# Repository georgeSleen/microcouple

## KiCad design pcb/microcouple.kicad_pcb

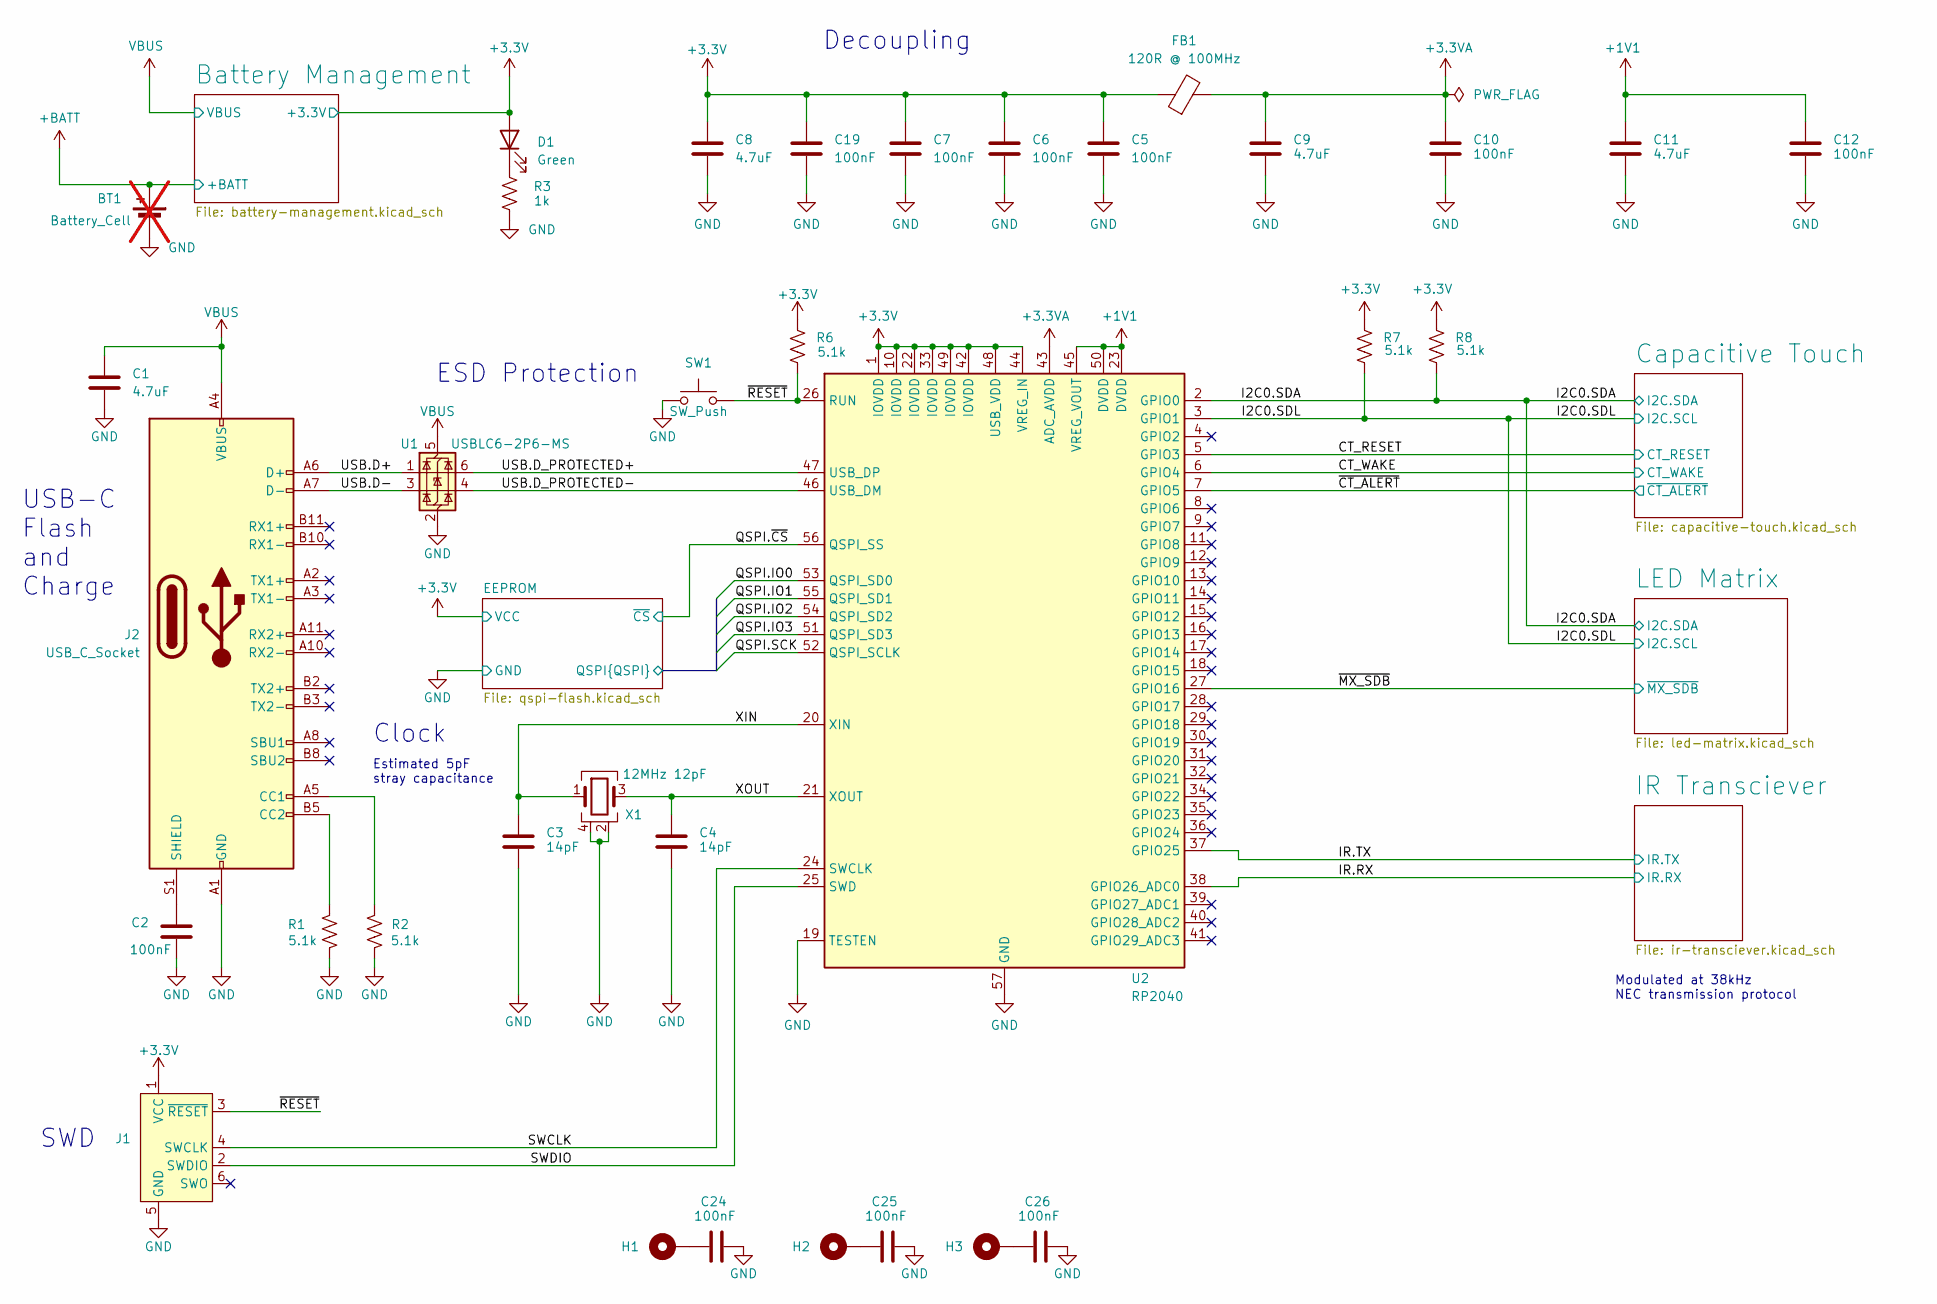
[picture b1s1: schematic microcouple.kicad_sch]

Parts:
BT1: Battery_Cell; PinSocket_2x01_P1.27mm_Vertical; not fitted
C1, C8, C9, C11: 4.7uF; C_0402_1005Metric; Mfr. Part # GRM155R60J475ME87D; LCSC ID C76996
C2, C5, C6, C7, C10, C12, C19, C24, C25, C26: 100nF; C_0402_1005Metric; Mfr. Part # TCC0402X5R104K160AT; LCSC ID C344189
C3, C4: 14pF; C_0402_1005Metric; Mfr. Part # 0402CG140J500NT; LCSC ID C3037644
D1: Green; LED_0402_1005Metric; Mfr. Part # XL-1005UGC; LCSC ID C965793
FB1: 120R @ 100MHz; L_0805_2012Metric; Mfr. Part # HCB2012KF-121T30; LCSC ID C356987
H1, H2, H3: MountingHole_Pad; MountingHole_2.2mm_M2_DIN965_Pad
J1: Conn_ARM_SWD_TagConnect_TC2030-NL; Tag-Connect_TC2030-IDC-NL_2x03_P1.27mm_Vertical
J2: USB_C_Socket; USB-C-SMD; Mfr. Part # TYPE-C 24P QT; LCSC ID C2681555
R1, R2, R6, R7, R8: 5.1k; R_0402_1005Metric; Mfr. Part # RC-02K512JT; LCSC ID C453708
R3: 1k; R_0402_1005Metric; Mfr. Part # FRC0402J102 TS; LCSC ID C2906899
SW1: SW_Push; SW_SPST_B3U-1000P; Mfr. Part # B3U-1000P; LCSC ID C231329
U1: USBLC6-2P6-MS; SOT-666; Mfr. Part # USBLC6-2P6; LCSC ID C2827693
U2: RP2040; QFN-56-1EP_7x7mm_P0.4mm_EP3.2x3.2mm; Mfr. Part # RP2040; LCSC ID C2040
X1: 12MHz 12pF; Crystal_SMD_3225-4Pin_3.2x2.5mm; Mfr. Part # TAXM12M4RFBCCT2T; LCSC ID C133337

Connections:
+1V1: C11.1, C12.1, U2.23 (DVDD), U2.45 (VREG_VOUT), U2.50 (DVDD)
+3.3V: C5.1, C6.1, C7.1, C8.1, C19.1, D1.2 (A), FB1.1, J1.1 (VCC), R6.1, R7.1, R8.1, U2.1 (IOVDD), U2.10 (IOVDD), U2.22 (IOVDD), U2.33 (IOVDD), U2.42 (IOVDD), U2.44 (VREG_IN), U2.48 (USB_VDD), U2.49 (IOVDD); also elsewhere on the board
+3.3VA: C9.1, C10.1, FB1.2, U2.43 (ADC_AVDD)
+BATT: BT1.1 (+); also elsewhere on the board
/CT_RESET: U2.5 (GPIO3); also elsewhere on the board
/CT_WAKE: U2.6 (GPIO4); also elsewhere on the board
/EEPROM/QSPI.IO0: U2.53 (QSPI_SD0); also elsewhere on the board
/EEPROM/QSPI.IO1: U2.55 (QSPI_SD1); also elsewhere on the board
/EEPROM/QSPI.IO2: U2.54 (QSPI_SD2); also elsewhere on the board
/EEPROM/QSPI.IO3: U2.51 (QSPI_SD3); also elsewhere on the board
/EEPROM/QSPI.SCK: U2.52 (QSPI_SCLK); also elsewhere on the board
/I2C0.SDA: R8.2, U2.2 (GPIO0); also elsewhere on the board
/I2C0.SDL: R7.2, U2.3 (GPIO1); also elsewhere on the board
/IR.RX: U2.38 (GPIO26_ADC0); also elsewhere on the board
/IR.TX: U2.37 (GPIO25); also elsewhere on the board
/QSPI.~CS: U2.56 (QSPI_SS); also elsewhere on the board
/SWCLK: J1.4 (SWCLK), U2.24 (SWCLK)
/SWDIO: J1.2 (SWDIO), U2.25 (SWD)
/USB.D+: J2.A6 (D+), J2.B6 (D+), U1.1 (I/O1)
/USB.D-: J2.A7 (D-), J2.B7 (D-), U1.3 (I/O2)
/USB.D_PROTECTED+: U1.6 (I/O1), U2.47 (USB_DP)
/USB.D_PROTECTED-: U1.4 (I/O2), U2.46 (USB_DM)
/XIN: C3.1, U2.20 (XIN), X1.1
/XOUT: C4.1, U2.21 (XOUT), X1.3
/~CT_ALERT: U2.7 (GPIO5); also elsewhere on the board
/~MX_SDB: U2.27 (GPIO16); also elsewhere on the board
/~RESET: J1.3 (~RESET), R6.2, SW1.2, U2.26 (RUN)
GND: BT1.2 (-), C1.2, C2.2, C3.2, C4.2, C5.2, C6.2, C7.2, C8.2, C9.2, C10.2, C11.2, C12.2, C19.2, C24.2, C25.2, C26.2, J1.5 (GND), J2.A1 (GND), J2.A12 (GND), J2.B1 (GND), J2.B12 (GND), R1.2, R2.1, R3.2, SW1.1, U1.2 (GND), U2.19 (TESTEN), U2.57 (GND), X1.2, X1.4; also elsewhere on the board
unnamed: C24.1, H1.1
unnamed: C25.1, H2.1
unnamed: C26.1, H3.1
unnamed: D1.1 (K), R3.1
unnamed: J2.A5 (CC1), R2.2
unnamed: J2.B5 (CC2), R1.1
unnamed: C2.1, J2.S1 (SHIELD)
VBUS: C1.1, J2.A4 (VBUS), J2.A9 (VBUS), J2.B4 (VBUS), J2.B9 (VBUS), U1.5 (VBUS); also elsewhere on the board

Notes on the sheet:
Decoupling
Estimated 5pF stray capacitance
USB-C Flash and Charge
Clock
SWD
Modulated at 38kHz NEC transmission protocol
ESD Protection

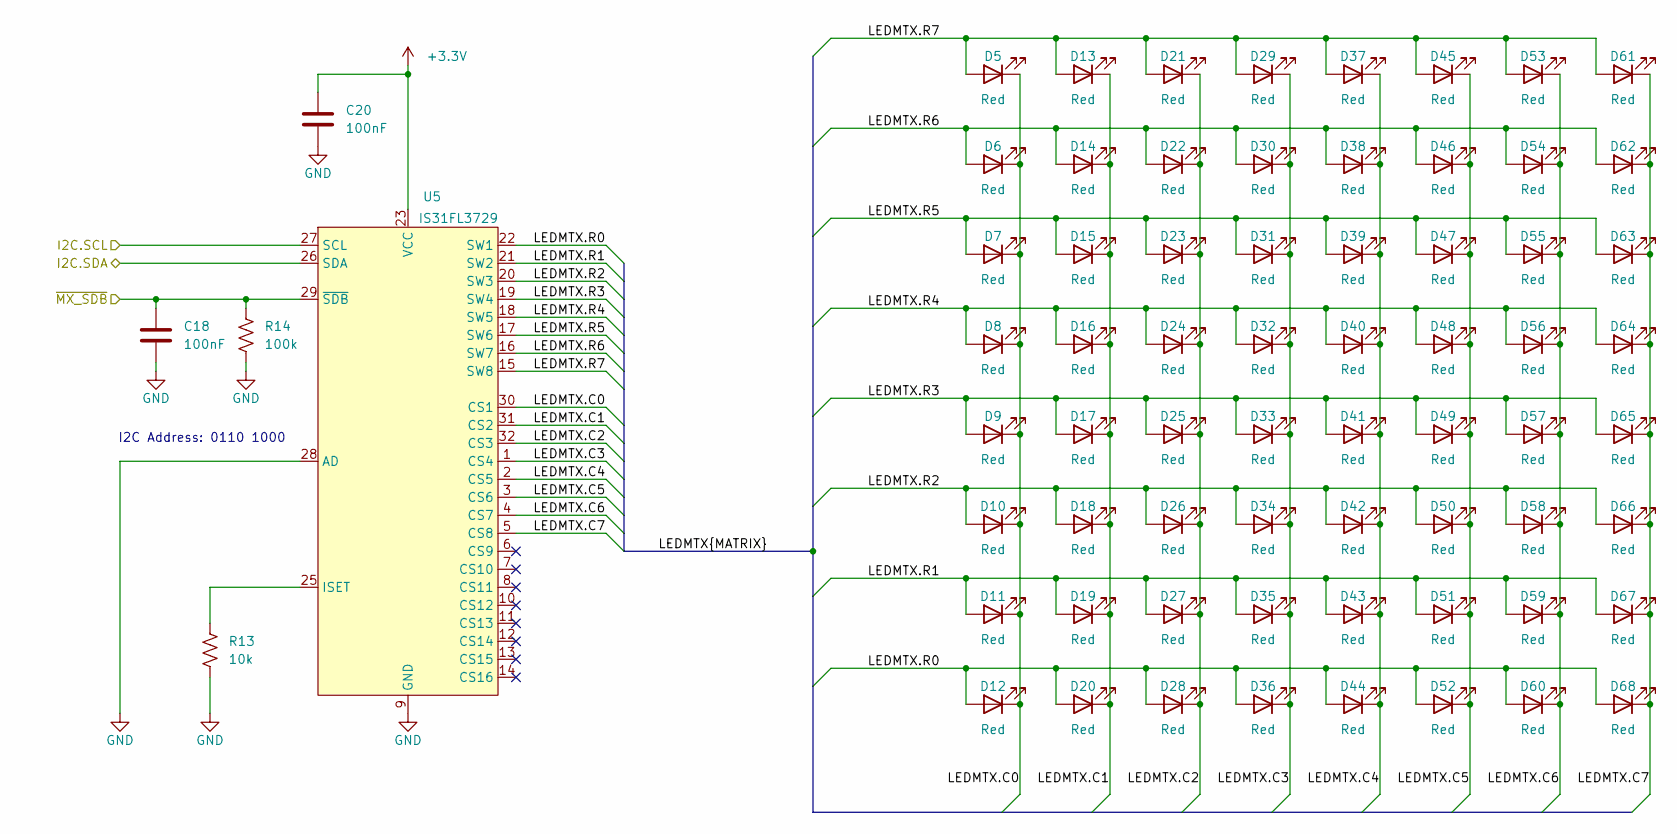
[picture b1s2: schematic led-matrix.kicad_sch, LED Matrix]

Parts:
C18, C20: 100nF; C_0402_1005Metric; Mfr. Part # TCC0402X5R104K160AT; LCSC ID C344189
D5, D6, D7, D8, D9, D10, D11, D12, D13, D14, D15, D16, D17, D18, D19, D20, D21, D22, D23, D24, D25, D26, D27, D28, D29, D30, D31, D32, D33, D34, D35, D36, D37, D38, D39, D40, D41, D42, D43, D44, D45, D46, D47, D48, D49, D50, D51, D52, D53, D54, D55, D56, D57, D58, D59, D60, D61, D62, D63, D64, D65, D66, D67, D68: Red; LED_0402_1005Metric; Mfr. Part # XL-1005SURC; LCSC ID C965790
R13: 10k; R_0402_1005Metric; Mfr. Part # RTT02103JTH; LCSC ID C102759
R14: 100k; R_0402_1005Metric; Mfr. Part # SCR0402J100K; LCSC ID C3017514
U5: IS31FL3729; QFN-32-1EP_4x4mm_P0.4mm_EP2.65x2.65mm; Mfr. Part # IS31FL3729-QFLS4-TR; LCSC ID C2940549

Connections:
+3.3V: C20.1, U5.23 (VCC); also elsewhere on the board
/I2C0.SDA: U5.26 (SDA); also elsewhere on the board
/I2C0.SDL: U5.27 (SCL); also elsewhere on the board
/LED Matrix/LEDMTX.C0: D5.1 (K), D6.1 (K), D7.1 (K), D8.1 (K), D9.1 (K), D10.1 (K), D11.1 (K), D12.1 (K), U5.30 (CS1)
/LED Matrix/LEDMTX.C1: D13.1 (K), D14.1 (K), D15.1 (K), D16.1 (K), D17.1 (K), D18.1 (K), D19.1 (K), D20.1 (K), U5.31 (CS2)
/LED Matrix/LEDMTX.C2: D21.1 (K), D22.1 (K), D23.1 (K), D24.1 (K), D25.1 (K), D26.1 (K), D27.1 (K), D28.1 (K), U5.32 (CS3)
/LED Matrix/LEDMTX.C3: D29.1 (K), D30.1 (K), D31.1 (K), D32.1 (K), D33.1 (K), D34.1 (K), D35.1 (K), D36.1 (K), U5.1 (CS4)
/LED Matrix/LEDMTX.C4: D37.1 (K), D38.1 (K), D39.1 (K), D40.1 (K), D41.1 (K), D42.1 (K), D43.1 (K), D44.1 (K), U5.2 (CS5)
/LED Matrix/LEDMTX.C5: D45.1 (K), D46.1 (K), D47.1 (K), D48.1 (K), D49.1 (K), D50.1 (K), D51.1 (K), D52.1 (K), U5.3 (CS6)
/LED Matrix/LEDMTX.C6: D53.1 (K), D54.1 (K), D55.1 (K), D56.1 (K), D57.1 (K), D58.1 (K), D59.1 (K), D60.1 (K), U5.4 (CS7)
/LED Matrix/LEDMTX.C7: D61.1 (K), D62.1 (K), D63.1 (K), D64.1 (K), D65.1 (K), D66.1 (K), D67.1 (K), D68.1 (K), U5.5 (CS8)
/LED Matrix/LEDMTX.R0: D12.2 (A), D20.2 (A), D28.2 (A), D36.2 (A), D44.2 (A), D52.2 (A), D60.2 (A), D68.2 (A), U5.22 (SW1)
/LED Matrix/LEDMTX.R1: D11.2 (A), D19.2 (A), D27.2 (A), D35.2 (A), D43.2 (A), D51.2 (A), D59.2 (A), D67.2 (A), U5.21 (SW2)
/LED Matrix/LEDMTX.R2: D10.2 (A), D18.2 (A), D26.2 (A), D34.2 (A), D42.2 (A), D50.2 (A), D58.2 (A), D66.2 (A), U5.20 (SW3)
/LED Matrix/LEDMTX.R3: D9.2 (A), D17.2 (A), D25.2 (A), D33.2 (A), D41.2 (A), D49.2 (A), D57.2 (A), D65.2 (A), U5.19 (SW4)
/LED Matrix/LEDMTX.R4: D8.2 (A), D16.2 (A), D24.2 (A), D32.2 (A), D40.2 (A), D48.2 (A), D56.2 (A), D64.2 (A), U5.18 (SW5)
/LED Matrix/LEDMTX.R5: D7.2 (A), D15.2 (A), D23.2 (A), D31.2 (A), D39.2 (A), D47.2 (A), D55.2 (A), D63.2 (A), U5.17 (SW6)
/LED Matrix/LEDMTX.R6: D6.2 (A), D14.2 (A), D22.2 (A), D30.2 (A), D38.2 (A), D46.2 (A), D54.2 (A), D62.2 (A), U5.16 (SW7)
/LED Matrix/LEDMTX.R7: D5.2 (A), D13.2 (A), D21.2 (A), D29.2 (A), D37.2 (A), D45.2 (A), D53.2 (A), D61.2 (A), U5.15 (SW8)
/~MX_SDB: C18.1, R14.1, U5.29 (~SDB); also elsewhere on the board
GND: C18.2, C20.2, R13.2, R14.2, U5.9 (GND), U5.24 (GND), U5.28 (AD), U5.33 (GND); also elsewhere on the board
unnamed: R13.1, U5.25 (ISET)

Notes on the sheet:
I2C Address: 0110 1000

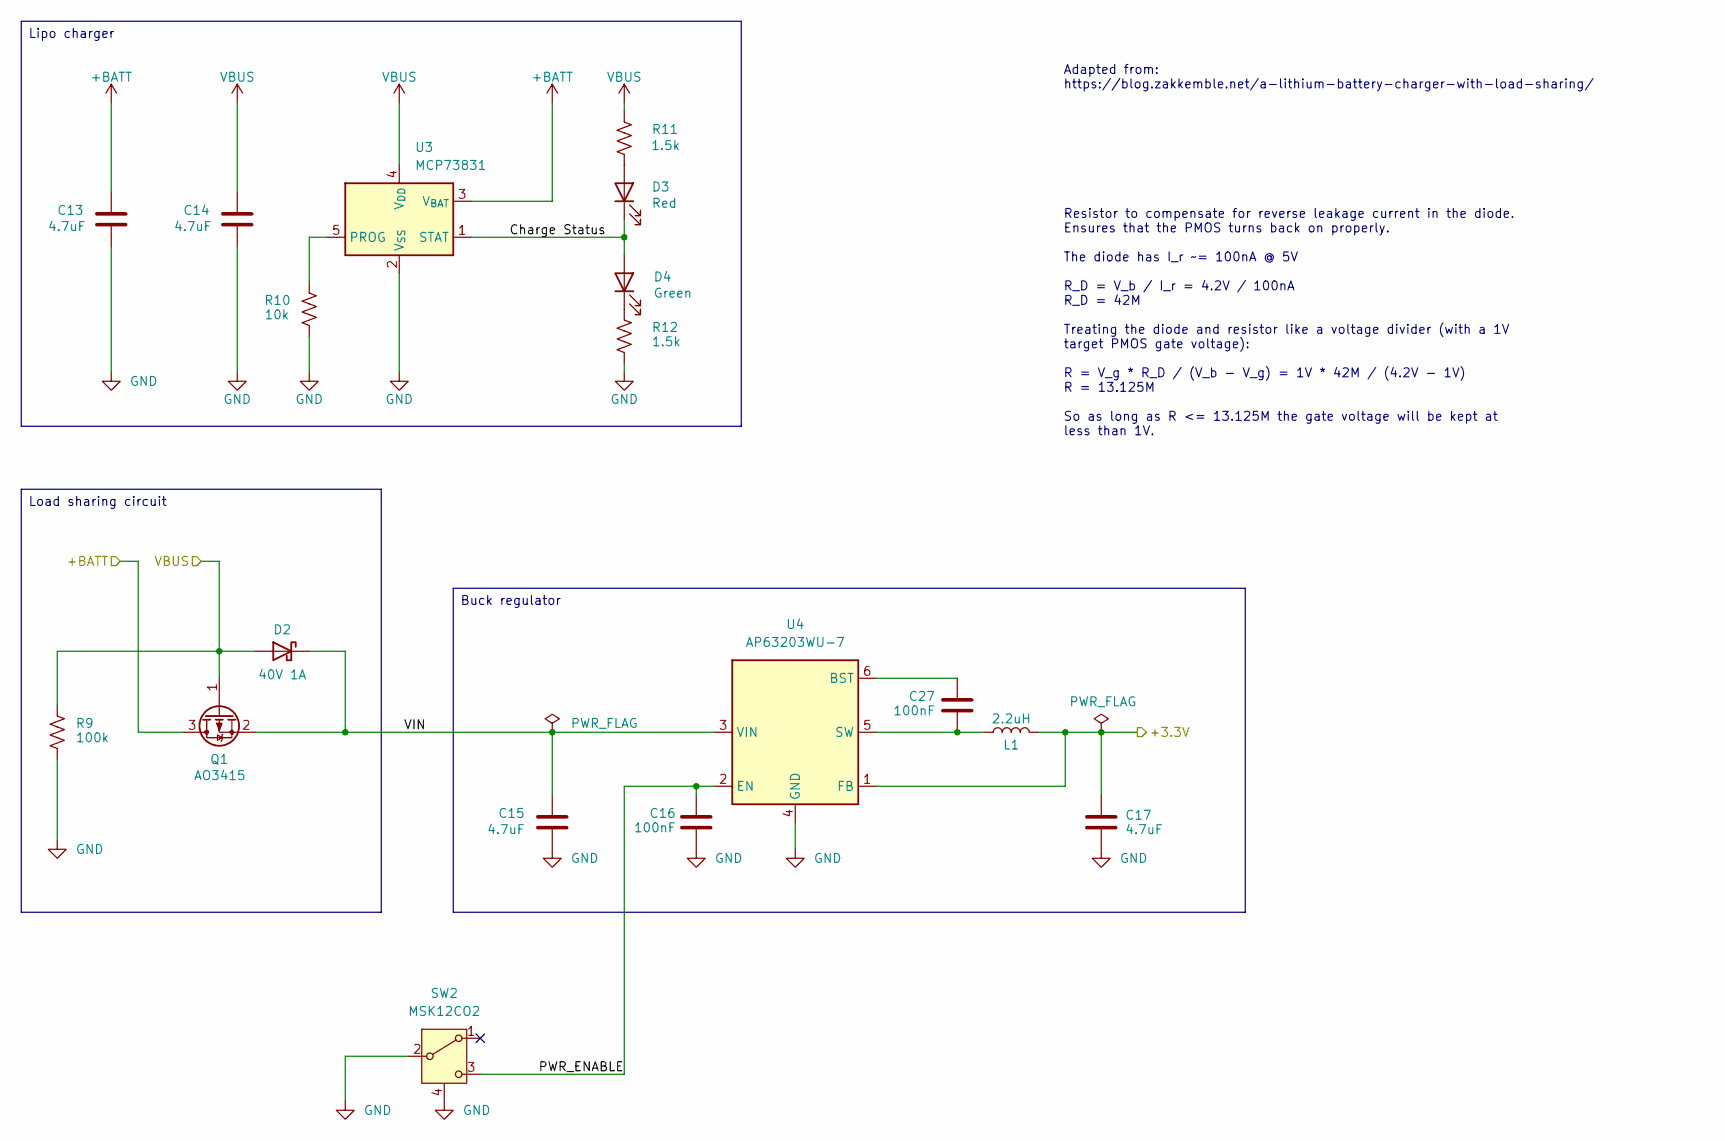
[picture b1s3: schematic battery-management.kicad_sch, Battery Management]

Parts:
C13, C14, C15, C17: 4.7uF; C_0402_1005Metric; Mfr. Part # GRM155R60J475ME87D; LCSC ID C76996
C16, C27: 100nF; C_0402_1005Metric; Mfr. Part # TCC0402X5R104K160AT; LCSC ID C344189
D2: 40V 1A; D_SOD-123; Mfr. Part # 1N5819W; LCSC ID C41431973
D3: Red; LED_0402_1005Metric; Mfr. Part # XL-1005SURC; LCSC ID C965790
D4: Green; LED_0402_1005Metric; Mfr. Part # XL-1005UGC; LCSC ID C965793
L1: 2.2uH; L_1008_2520Metric; Mfr. Part # PNR252012-2R2M; LCSC ID C19634045
Q1: AO3415; SOT-23; Mfr. Part # AO3415; LCSC ID C840839
R9: 100k; R_0402_1005Metric; Mfr. Part # SCR0402J100K; LCSC ID C3017514
R10: 10k; R_0402_1005Metric; Mfr. Part # RTT02103JTH; LCSC ID C102759
R11, R12: 1.5k; R_0402_1005Metric; Mfr. Part # FRC0402J152TS; LCSC ID C2929900
SW2: MSK12CO2; Mfr. Part # MINI MSK12CO2; LCSC ID C2681570
U3: MCP73831; SOT-23-5; Mfr. Part # MCP73831T-2ACI/OT; LCSC ID C424093
U4: AP63203WU-7; TSOT-23-6; Mfr. Part # AP63203WU-7; LCSC ID C780769

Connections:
+3.3V: C17.1, L1.2, U4.1 (FB); also elsewhere on the board
+BATT: C13.1, Q1.3 (D), U3.3 (V_{BAT}); also elsewhere on the board
/Battery Management/Charge Status: D3.1 (K), D4.2 (A), U3.1 (STAT)
/Battery Management/PWR_ENABLE: C16.1, SW2.3 (C), U4.2 (EN)
/Battery Management/VIN: C15.1, D2.1 (K), Q1.2 (S), U4.3 (VIN)
GND: C13.2, C14.2, C15.2, C16.2, C17.2, R9.2, R10.2, R12.1, SW2.2 (B), SW2.4 (Shield), U3.2 (V_{SS}), U4.4 (GND); also elsewhere on the board
unnamed: D3.2 (A), R11.1
unnamed: D4.1 (K), R12.2
unnamed: R10.1, U3.5 (PROG)
unnamed: C27.1, U4.6 (BST)
unnamed: C27.2, L1.1, U4.5 (SW)
VBUS: C14.1, D2.2 (A), Q1.1 (G), R9.1, R11.2, U3.4 (V_{DD}); also elsewhere on the board

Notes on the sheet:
Adapted from: https://blog.zakkemble.net/a-lithium-battery-charger-with-load-sharing/
Buck regulator
Load sharing circuit
Lipo charger
Resistor to compensate for reverse leakage current in the diode. Ensures that the PMOS turns back on properly. The diode has I_r ~= 100nA @ 5V R_D = V_b / I_r = 4.2V / 100nA R_D = 42M Treating the diode and resistor like a voltage divider (with a 1V target PMOS gate voltage): R = V_g * R_D / (V_b -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

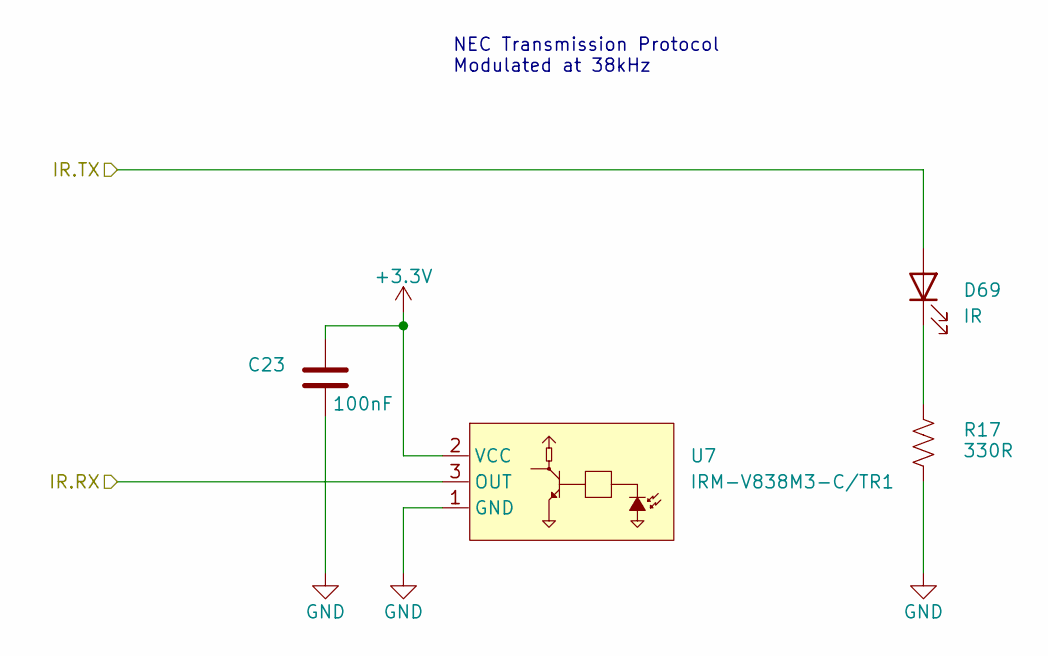
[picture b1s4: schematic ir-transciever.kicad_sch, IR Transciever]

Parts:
C23: 100nF; C_0402_1005Metric; Mfr. Part # TCC0402X5R104K160AT; LCSC ID C344189
D69: IR; LED_SMD_L3.0-W2.7-RD; Mfr. Part # IR26-61C/L302/TR8; LCSC ID C181893
R17: 330R; R_0402_1005Metric; Mfr. Part # FRC0402J331 TS; LCSC ID C2906929
U7: IRM-V838M3-C/TR1; IRM-V8__M3-C-TR1; Mfr. Part # IRM-V838M3-C/TR1; LCSC ID C3291489

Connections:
+3.3V: C23.1, U7.2 (VCC); also elsewhere on the board
/IR.RX: U7.3 (OUT); also elsewhere on the board
/IR.TX: D69.2 (A); also elsewhere on the board
GND: C23.2, R17.2, U7.1 (GND), U7.4 (GND); also elsewhere on the board
unnamed: D69.1 (K), R17.1

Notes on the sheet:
NEC Transmission Protocol Modulated at 38kHz

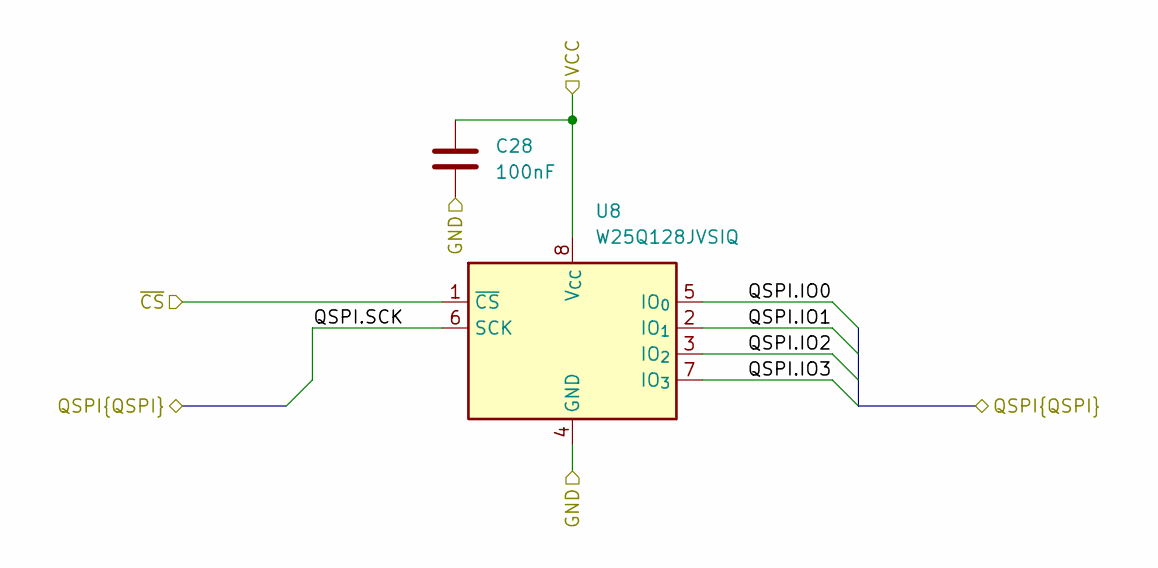
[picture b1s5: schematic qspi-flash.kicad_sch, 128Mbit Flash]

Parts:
C28: 100nF; C_0402_1005Metric; Mfr. Part # TCC0402X5R104K160AT; LCSC ID C344189
U8: W25Q128JVSIQ; SOIC-8_5.3x5.3mm_P1.27mm; Mfr. Part # W25Q128JVSIQ; LCSC ID C97521

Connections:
+3.3V: C28.1, U8.8 (V_{CC}); also elsewhere on the board
/EEPROM/QSPI.IO0: U8.5 (IO_{0}); also elsewhere on the board
/EEPROM/QSPI.IO1: U8.2 (IO_{1}); also elsewhere on the board
/EEPROM/QSPI.IO2: U8.3 (IO_{2}); also elsewhere on the board
/EEPROM/QSPI.IO3: U8.7 (IO_{3}); also elsewhere on the board
/EEPROM/QSPI.SCK: U8.6 (SCK); also elsewhere on the board
/QSPI.~CS: U8.1 (~CS); also elsewhere on the board
GND: C28.2, U8.4 (GND); also elsewhere on the board

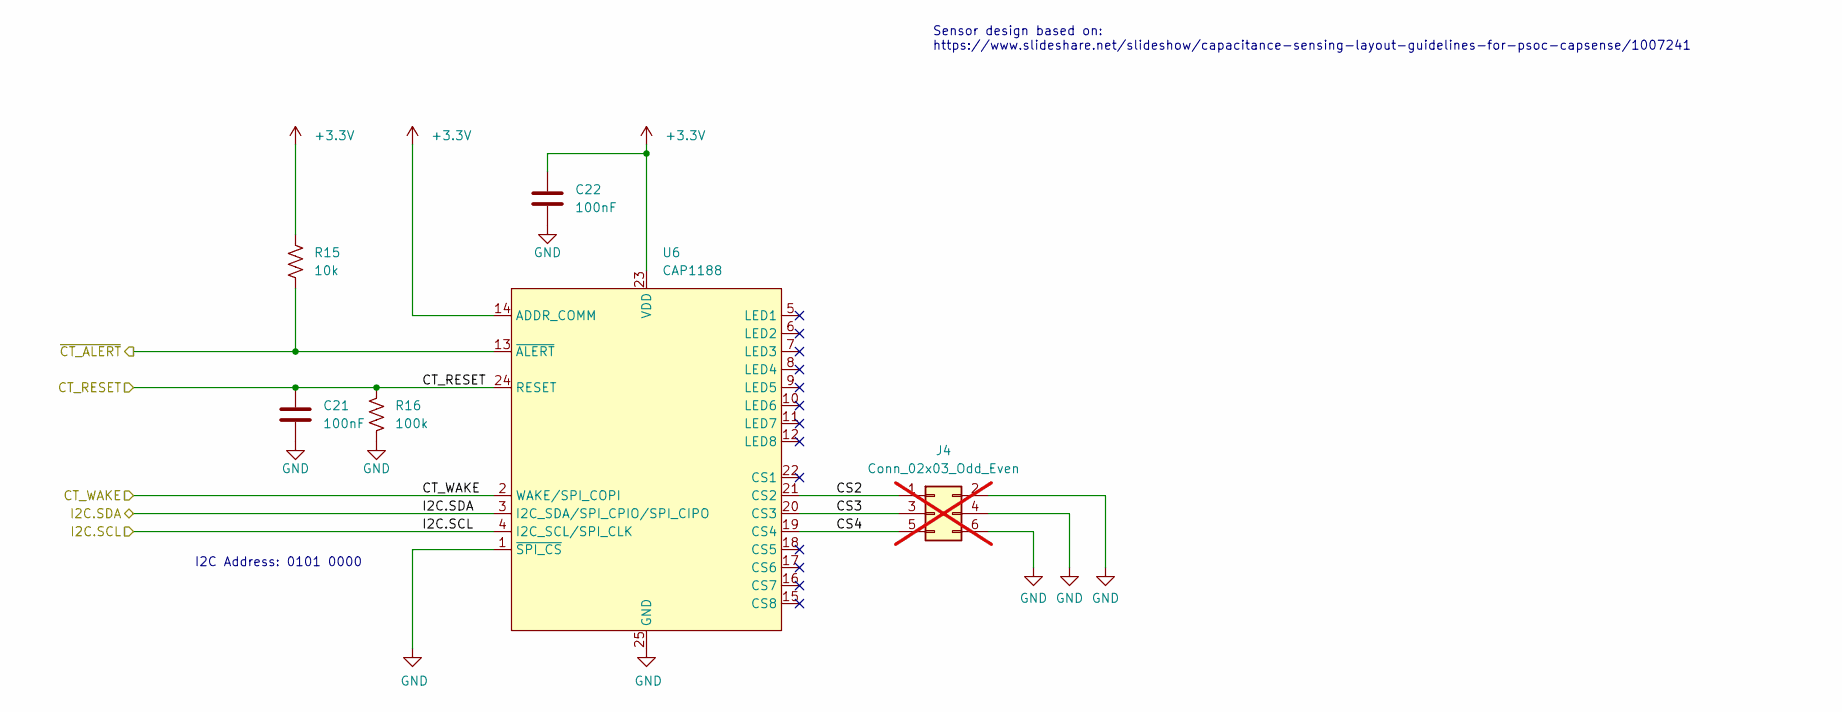
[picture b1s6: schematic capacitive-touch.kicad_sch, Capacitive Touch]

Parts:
C21, C22: 100nF; C_0402_1005Metric; Mfr. Part # TCC0402X5R104K160AT; LCSC ID C344189
J4: Conn_02x03_Odd_Even; PinHeader_2x03_P1.27mm_Vertical; not fitted
R15: 10k; R_0402_1005Metric; Mfr. Part # RTT02103JTH; LCSC ID C102759
R16: 100k; R_0402_1005Metric; Mfr. Part # SCR0402J100K; LCSC ID C3017514
U6: CAP1188; QFN-24-1EP_4x4mm_P0.5mm_EP2.5x2.5mm; Mfr. Part # CAP1188-1-CP-TR; LCSC ID C2652057

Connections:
+3.3V: C22.1, R15.1, U6.14 (ADDR_COMM), U6.23 (VDD); also elsewhere on the board
/CT_RESET: C21.1, R16.1, U6.24 (RESET); also elsewhere on the board
/CT_WAKE: U6.2 (WAKE/SPI_COPI); also elsewhere on the board
/Capacitive Touch/CS2: J4.1, U6.21 (CS2)
/Capacitive Touch/CS3: J4.3, U6.20 (CS3)
/Capacitive Touch/CS4: J4.5, U6.19 (CS4)
/I2C0.SDA: U6.3 (I2C_SDA/SPI_CPIO/SPI_CIPO); also elsewhere on the board
/I2C0.SDL: U6.4 (I2C_SCL/SPI_CLK); also elsewhere on the board
/~CT_ALERT: R15.2, U6.13 (~ALERT); also elsewhere on the board
GND: C21.2, C22.2, J4.2, J4.4, J4.6, R16.2, U6.1 (~SPI_CS), U6.25 (GND); also elsewhere on the board

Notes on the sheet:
I2C Address: 0101 0000
Sensor design based on: https://www.slideshare.net/slideshow/capacitance-sensing-layout-guidelines-for-psoc-capsense/1007241

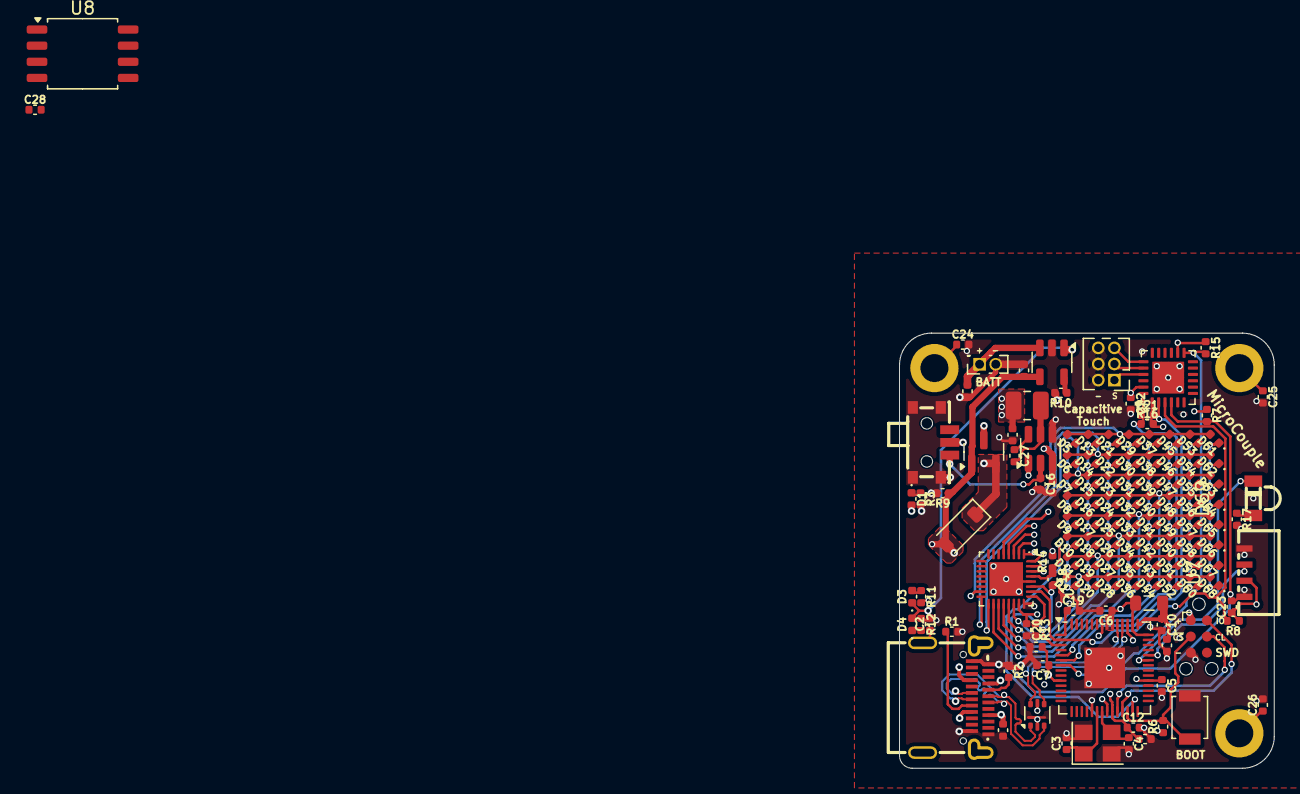
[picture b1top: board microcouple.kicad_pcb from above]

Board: 4 copper layers, 29.5 x 34.2 mm, 133 parts (0 on the bottom side), 65 nets.

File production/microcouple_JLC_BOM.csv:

"Reference","Value","Qty","LCSC ID","Manufacturer","Mfr. Part #","Package","DNP","Exclude from BOM"
"C1,C8,C9,C11,C13,C14,C15,C17","4.7uF","8","C76996","Murata Electronics","GRM155R60J475ME87D","0402","",""
"C2,C5,C6,C7,C10,C12,C16,C18,C19,C20,C21,C22,C23,C24,C25,C26,C27","100nF","17","C18164587","CCTC","TCC0201X5R104M250ZT","0201","",""
"C3,C4","14pF","2","C3037637","FH (Guangdong Fenghua Advanced Tech)","0201CG140J500NT","0201","",""
"D1,D4","Green","2","C3646922","XINGLIGHT","XL-0201UGC","0201","",""
"D2","40V 1A","1","C41431973","GOODWORK","1N5819W","SOD-123","",""
"D3,D5,D6,D7,D8,D9,D10,D11,D12,D13,D14,D15,D16,D17,D18,D19,D20,D21,D22,D23,D24,D25,D26,D27,D28,D29,D30,D31,D32,D33,D34,D35,D36,D37,D38,D39,D40,D41,D42,D43,D44,D45,D46,D47,D48,D49,D50,D51,D52,D53,D54,D55,D56,D57,D58,D59,D60,D61,D62,D63,D64,D65,D66,D67,D68","Red","65","C3646923","XINGLIGHT","XL-0201SURC","0201","",""
"D69","IR","1","C181893","Everlight Elec","IR26-61C/L302/TR8","SMD,2.7x3mm","",""
"FB1","120R @ 100MHz","1","C356987","TAI-TECH","HCB2012KF-121T30","0805","",""
"H1,H2,H3","MountingHole_Pad","3","","","","","","Excluded from BOM"
"J1","Conn_ARM_SWD_TagConnect_TC2030-NL","1","","","","","","Excluded from BOM"
"J2","USB_C_Socket","1","C2681555","SHOU HAN","TYPE-C 24P QT","SMD","",""
"L1","2.2uH","1","C19634045","APV","PNR252012-2R2M","1008","",""
"Q1","AO3415","1","C840839","MDD(Microdiode Semiconductor)","AO3415","SOT-23","",""
"R1,R2,R6,R7,R8","5.1k","5","C158467","RALEC","RTT01512JTH","0201","",""
"R3","1k","1","C304503","FH (Guangdong Fenghua Advanced Tech)","RC-01W102JT","0201","",""
"R9,R14,R16","100k","3","C106224","YAGEO","RC0201FR-07100KL","0201","",""
"R10,R13,R15","10k","3","C304504","FH (Guangdong Fenghua Advanced Tech)","RC-01W103JT","0201","",""
"R11,R12","1.5k","2","C270328","UNI-ROYAL(Uniroyal Elec)","0201WMJ0152TEE","0201","",""
"R17","330R","1","C320833","FH (Guangdong Fenghua Advanced Tech)","RC-01W3300FT","0201","",""
"SW1","SW_Push","1","C231329","Omron Electronics","B3U-1000P","SMD, 2.5x3mm","",""
"SW2","MSK12CO2","1","C2681570","SHOU HAN","MINI MSK12CO2","SMD","",""
"U1","USBLC6-2P6-MS","1","C2827693","TECH PUBLIC","USBLC6-2P6","SOT-666-6","",""
"U2","RP2040","1","C2040","Raspberry Pi","RP2040","LQFN-56(7x7)","",""
"U3","MCP73831","1","C424093","Microchip Tech","MCP73831T-2ACI/OT","SOT-23-5","",""
"U4","AP63203WU-7","1","C780769","Diodes Incorporated","AP63203WU-7","TSOT-23-6","",""
"U5","IS31FL3729","1","C2940549","ISSI(Integrated Silicon Solution)","IS31FL3729-QFLS4-TR","QFN-32-EP(4x4)","",""
"U6","CAP1188","1","C2652057","Microchip Tech","CAP1188-1-CP-TR","QFN-24-EP(4x4)","",""
"U7","IRM-V838M3-C/TR1","1","C3291489","Everlight Elec","IRM-V838M3-C/TR1","SMD-4P,3x6.6mm","",""
"X1","12MHz 12pF","1","C133337","Yajingxin","TAXM12M4RFBCCT2T","SMD3225-4P","",""

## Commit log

2025-02-02 Create functional blocks
2025-02-02 Add decoupling caps on MCU
2025-02-03 Sketch out IR transceiver
2025-02-03 Sketch out LED matrix
2025-02-03 First draft of LED matrix
2025-03-04 Finalize battery management
2025-03-04 Finish base MCU design
2025-03-09 Preliminary Schematic
2025-03-21 Switch THT IR components to SMD ones
2025-03-21 Preliminary layout
2025-03-27 Fix faulty USB-C CC pin connections
2025-04-23 Draft layout
2025-04-25 Finish Silkscreen
2025-04-25 Finish layout
2025-04-28 Update for JLCPCB
2025-04-28 Create JLC CPL and BOM
2025-04-28 Small fix to JLC BOM
2025-04-28 Change missing part on JLC
2025-04-28 Change all components to 0402 if smaller
2025-05-15 Stop production outputs from being ignored...
2025-05-15 Generate production outputs for 0201 components
2025-05-25 Refactor project structure
2025-06-26 Prepare schematic for revision 2.0.0
2025-06-26 Update BOM settings
2025-11-13 Generate drawings
